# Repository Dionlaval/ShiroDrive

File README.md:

# ShiroDrive

ShiroDrive is an independent motion-control project focused on modular motor-drive hardware and experimental robotic systems.

The current hardware direction includes both stepper control and compact, networked FOC servo modules.

This is an evolving engineering project.

---

## Core Direction

ShiroDrive currently explores:

- Custom stepper motor driver design
- Dynamic microstepping techniques
- Smooth motion across wide velocity ranges
- Resonance mitigation and control refinement
- CoreXY motion architectures

The stepper platform uses ESP32, while ShiroFOC is based on the STSPIN32G4 with its embedded STM32G431 motor-control MCU.

ESP32 provides:

- Real-time capable control
- Flexible peripheral configuration
- Wireless debugging and telemetry
- Rapid prototyping flexibility

STSPIN32G4 provides:

- Integrated STM32G4 real-time motor-control MCU
- Three external-MOSFET gate drivers
- Integrated current-sense op-amps and hardware protection comparators
- CAN-based modular communication
- Compact single-axis FOC architecture

---

## Building Block

### ShiroDrive Step

A custom stepper motor control platform.

Focus areas:

- Dynamic microstepping
- High-speed stability
- Clean current control
- Modular PCB design
- Firmware-driven motion refinement

This board forms the foundation of all current machines.

### ShiroFOC

A single-axis, 48 V-class FOC servo module for robotics.

Planned features include:

- STSPIN32G4 controller and external three-phase MOSFET bridge
- Three-shunt phase-current sensing
- CAN communication to a coordinating motherboard
- Integrated magnetic encoder and 6-axis IMU
- External Hall and encoder inputs
- SWD programming and debug

See [ShiroFOC design constraints](ShiroFOC/docs/DESIGN_CONSTRAINTS.md) for the preliminary Rev A targets.

---

## Experimental Machine

### Manga Draw

A CoreXY-based pen plotting platform.

Purpose:

- Investigate high-speed planar motion
- Develop scalable XY architecture
- Render anime-style posters and manga panels with precision
- Serve as a validation platform for ShiroDrive Step

The architecture is designed to scale beyond desktop format.

---

## Development Status

### Currently Working On

- ShiroDrive Step PCB iteration
- Motion firmware development (ESP32)
- CoreXY Manga Draw platform integration

### Next Steps

- Refinement of dynamic microstepping
- Mechanical rigidity improvements
- Higher current driver revisions
- Closed-loop motion experimentation

---

ShiroDrive documents the process of building motion systems from first principles — hardware, firmware, and mechanical integration.

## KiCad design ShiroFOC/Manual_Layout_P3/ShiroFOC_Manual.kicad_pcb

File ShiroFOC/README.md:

# ShiroFOC workspace

## Start here

- **[Manual rebuild](Manual_Rebuild/ShiroFOC_Manual.kicad_pro)** — complete reference schematic with your manual MOSFET bridge retained, ready for page-by-page review; [library instructions](Manual_Rebuild/README.md).
- [P1 reference project](ShiroFOC_KiCad_P1/ShiroFOC_KiCad.kicad_pro) — existing schematic and revised component placement.
- [Saved routing review](routing_review_2026-09-21/README.md) — independent snapshots of the incomplete routing, paused for review.
- [Learning lab](../learning/README.md) — interactive models, exercises and explanations.

The original design files remain in their project folders. Routing is incomplete; the saved boards are not fabrication releases. The notes below document different design stages.

## Design notes

### Schematic and firmware

- **[Current firmware requirements](requirements/FIRMWARE_REQUIREMENTS.md)** — manual rebuild: safe startup, persistent BOOT0, calibration storage, sensors, current protection and brake control.

- [Design constraints](docs/DESIGN_CONSTRAINTS.md)
- [Rev A schematic plan](docs/SCHEMATIC_REV_A_PLAN.md)
- [Rev A design review](docs/DESIGN_REVIEW_REV_A.md)
- [Schematic readability plan](docs/SCHEMATIC_READABILITY_PLAN.md)
- [Schematic redraw review](docs/SCHEMATIC_REDRAW_REVIEW.md)
- [MCU pinout and interfaces](docs/MCU_PINOUT_AND_INTERFACE_PLAN.md)
- [Historical A0 firmware bring-up contract](docs/FIRMWARE_BRINGUP_CONTRACT.md)

### PCB

- [Layout guidelines and DRC settings](docs/PCB_LAYOUT_GUIDELINES.md)
- [Layout handoff](docs/PCB_LAYOUT_HANDOFF.md)
- [Original placement notes](docs/PCB_PLACEMENT_P0.md)
- [Revised placement notes](docs/PCB_PLACEMENT_P1.md)
- [P1 revision list](docs/PCB_REVISION_LIST_P1.md)
- [Capacitor options study](docs/PCB_CAPACITOR_OPTIONS_2026-09-17.md)

## Folder guide

| Folder | Contents |
|---|---|
| `Manual_Rebuild/` | Your schematic review copy, imported CAD and download checklist |
| `requirements/` | Current implementation requirements for the manual rebuild |
| `docs/` | Design plans, decisions and review notes |
| `ShiroFOC_KiCad/` | Original reference project and its outputs |
| `ShiroFOC_KiCad_P1/` | Revised placement project and routing experiments |
| `routing_review_2026-09-21/` | Saved routing checkpoints for inspection |
| `tools/` | Existing generation, checking and routing scripts |
| `backups/` | Preserved files, including the notes before this cleanup |

The documentation cleanup moved notes and repaired links; it did not change the existing circuitry or routing.

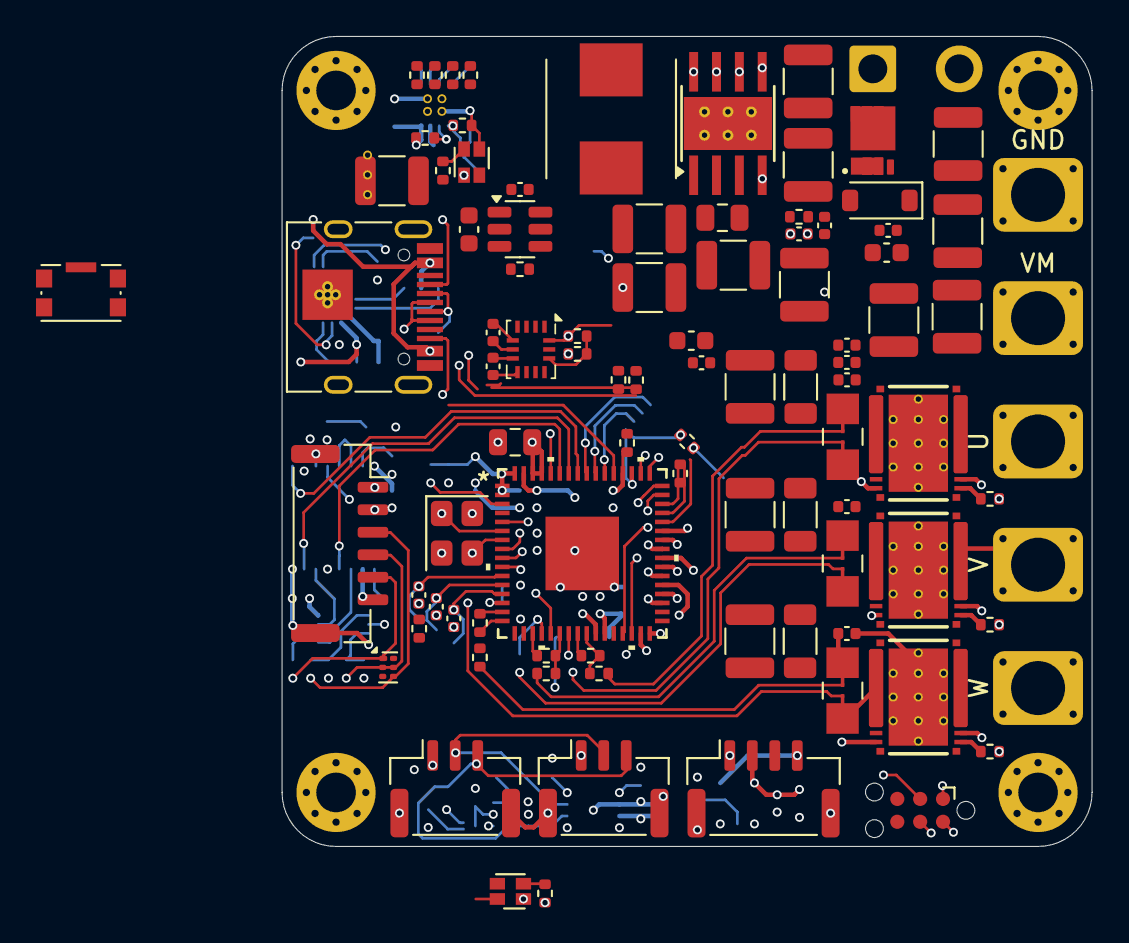
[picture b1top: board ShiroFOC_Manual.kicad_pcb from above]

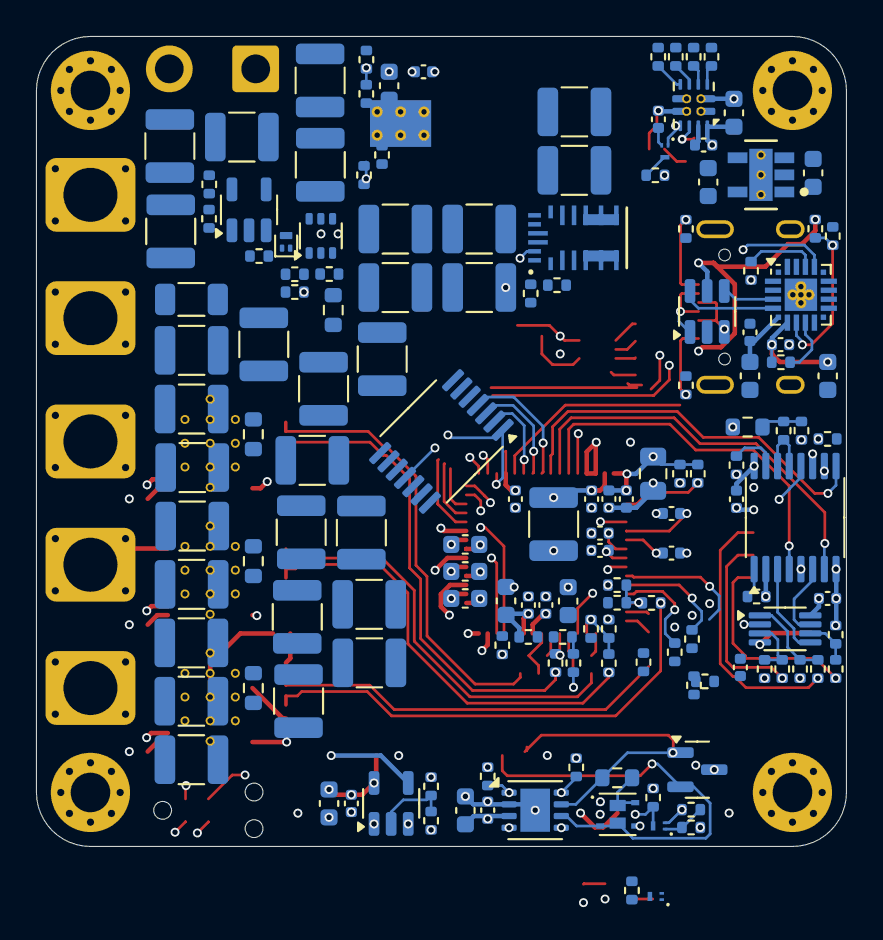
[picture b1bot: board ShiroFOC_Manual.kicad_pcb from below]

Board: 6 copper layers, 45.0 x 45.0 mm, 244 parts (149 on the bottom side), 142 nets.

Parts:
C1, C5, C9, C108, C314, C711, C712, C713: 10nF; C_0402_1005Metric
C2, C6, C10: 1uF; C_1206_3216Metric
C3, C7, C11, C101, C102, C110, C111, C112, C113, C114, C116, C117, C122, C123, C124, C127, C128, C129, C131, C133, C134, C135, C136, C137, C138, C144, C145, C146, C149, C150, C151, C152, C153, C154: 10uF; C_1210_3225Metric
C4, C8, C12: 220nF; C_0603_1608Metric
C104: 4.7uF 100V X7R; C_1210_3225Metric
C105: 100nF 100V X7R; C_0402_1005Metric
C106: 10nF 100V C0G; C_0402_1005Metric
C201: 2.2uF 100V X7R; C_1210_3225Metric
C202: 220nF 100V X7R; C_0805_2012Metric
C203, C209, C211, C301, C303, C305, C307, C310, C505, C601, C603, C605, C701, C702, C801, C902, C904: 100nF; C_0402_1005Metric
C204, C304, C306, C602, C802: 1uF; C_0603_1608Metric
C205, C206, C214, C215: 22uF 25V X7R; C_1210_3225Metric
C208: 1uF 10V; C_0603_1608Metric
C210: 22uF 10V X7R; C_1210_3225Metric
C212, C213: 2.2uF 10V X7R; C_0603_1608Metric
C218, C219: 22uF 16V X7R; C_1210_3225Metric
C302: 10uF 10V; C_0805_2012Metric
C308, C309: 10pF C0G; C_0402_1005Metric
C311: 220nF 100V; C_0805_2012Metric
C312: 10uF 25V X7R; C_1210_3225Metric
C313: 100nF 25V; C_0402_1005Metric
C501: 1uF 25V; C_0603_1608Metric
C502, C503, C604: 100nF 50V; C_0402_1005Metric
C504: 1nF C0G; C_0402_1005Metric
C506, C606: 4.7uF; C_0603_1608Metric
C607: 100nF 16V X7R; C_0402_1005Metric
C901, C903: 4.7uF 10V; C_0603_1608Metric
D201, D301: LTST-C19HE1WT; LED_LiteOn_LTST-C19HE1WT
D501: BZT52C12 12V; D_SOD-123
D502: BAT54CM; SOT-883
D601: TPD3E001DRYR; TPD3E001_DRY6
D801: PESD2CANFD24V-T; SOT-23
H1, H2, H3, H4: M2 PTH; MountingHole_2.2mm_M2_Pad_Via
J1: Motor phases - solder wires; WireSolder_Phase_1x03_P6.85mm_D3.00mm_Pad5.00x4.10mm_4xD0.4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
J101: DC input - solder wires; WireSolder_DC_1x02_P6.85mm_D3.00mm_Pad5.00x4.10mm_4xD0.40mm
J201: USB-C service; USB_C_Receptacle_HRO_TYPE-C-31-M-12
J501: BRAKE RESISTOR; SolderWire-0.75sqmm_1x02_P4.8mm_D1.25mm_OD2.3mm
J502: 5V PWM FAN; JST_GH_SM04B-GHS-TB_1x04-1MP_P1.25mm_Horizontal
J601: EXT ENCODER / HALL; JST_GH_SM06B-GHS-TB_1x06-1MP_P1.25mm_Horizontal
J801: CAN 1; JST_GH_SM03B-GHS-TB_1x03-1MP_P1.25mm_Horizontal
J802: CAN 2; JST_GH_SM03B-GHS-TB_1x03-1MP_P1.25mm_Horizontal
J1001: TC2030-NL SWD; Tag-Connect_TC2030-IDC-NL_2x03_P1.27mm_Vertical
L201: 47uH / 1.9A; WE_LHMI_7050_74437349470
Q201, Q301, Q801: CSD17483F4; CSD17483F4_YJC0003A
Q501: ISZ080N10NM6 100V; ISZ080N10NM6_TSDSON8_FL
Q802: CSD87502Q2; CSD87502Q2_DLV0006A
R1, R3, R5: 0.5m 1%; R_Shunt_HCS1206_0m5_2W_Kelvin
R2, R4, R6: 4R7; R_0402_1005Metric
R101: 470k 0.25W; R_1206_3216Metric
R103: 560k 0.1% 75V; R_0603_1608Metric
R105, R419, R429, R439: 28k 0.1%; R_0402_1005Metric
R106, R312, R711, R712, R713, R901: 1k; R_0402_1005Metric
R201: 100k 1%; R_0402_1005Metric
R202: 11.1k 1%; R_0402_1005Metric
R203, R204: 5.1k; R_0402_1005Metric
R206: 10.0k 1%; R_0402_1005Metric
R207, R209, R211, R213: 5.10k 1%; R_0402_1005Metric
R208: 15.0k 1%; R_0402_1005Metric
R210, R212: 22.0k 1%; R_0402_1005Metric
R214: 80.6k 1%; R_0402_1005Metric
R215, R220, R305, R306, R307, R309, R311, R315, R501, R504, R505, R604, R801, R805, R806: 10k; R_0402_1005Metric
R216: 34.0k 0.1%; R_0402_1005Metric
R217: 6.49k 0.1%; R_0402_1005Metric
R218, R219, R310, R512, R615, R616, R617, R804: 100k; R_0402_1005Metric
R221: 33k; R_0402_1005Metric
R301, R302: 0R; R_0402_1005Metric
R303: 2k2; R_0402_1005Metric
R304: 15k; R_0402_1005Metric
R308, R715: 2.2k; R_0402_1005Metric
R410, R420, R430, R441, R442, R443: 56k 0.1%; R_0402_1005Metric
R417, R418, R427, R428, R437, R438: 1k 0.1%; R_0402_1005Metric
R502: 33R; R_0402_1005Metric
R503: 4.7R; R_0402_1005Metric
R506: 470k 1% 75V; R_0603_1608Metric
R509: 13.3k 1%; R_0402_1005Metric
R510: 1M 1%; R_0402_1005Metric
R511, R605, R606, R607, R902, R903: 100R; R_0402_1005Metric
R618: 49.9k 1%; R_0402_1005Metric
R701, R702, R703: 4.7k 1%; R_0402_1005Metric
R802: 120R 1%; R_0603_1608Metric
R803: 4.7k; R_0402_1005Metric
R904: 22.1k 1%; R_0402_1005Metric
R905: 47.5k 1%; R_0402_1005Metric
SW301: RESET; SW_Push_1P1T-SH_NO_CK_KMR2xxG
TH701, TH702, TH703: 10k NTC B3380; R_0603_1608Metric
U1, U2, U3: CSD88599Q5DC; DMM0022A
U4: STSPIN32G4; QFN_IN32G4_STM
U201: LMR36510FADDAR; LMR36510_DDA
U202: USBLC6-2SC6; USBLC6_SOT23_6
U203: TPS2121RUXR; TPS2121_RUX
U204: TLV75533PDYDR; TLV75533_DYD_GND
U205: MPM3620AGQV-Z; IC18_MPM3620AGQV-Z_MNP
U501: UCC27517ADBVR; UCC27517A_DBV5
U502: TLV3012BIDCKR; SOT-363_SC-70-6
U503: 74AHCT1G125W5-7; SOT-23-5
U601: AS5047P-ATSM; AS5047P_TSSOP14
U602: TMUX1574PW; TMUX1574_PW16
U603: 74LVC3G17; VSSOP-8_2.3x2mm_P0.5mm
U604: TPS2553DBVR; SOT-23-6
U701: BMI323; BMI323_LGA14
U801: TCAN3413DRBR; TCAN3413_DRB8
U901: CP2102N-A02-GQFN20; SiliconLabs_QFN-20-1EP_3x3mm_P0.5mm_EP1.8x1.8mm_ThermalVias
Y301: 24MHz 7pF; Crystal_SMD_3225-4Pin_3.2x2.5mm

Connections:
3V3: C213.1, C301.1, C302.1, C307.1, C503.1, C601.1, C602.1, C603.1, C605.1, C701.1, C702.1, C801.1, C802.1, C901.1, C902.1, C903.1, C904.1, J1001.1 (VCC), R301.1, R303.1, R305.1, R308.1, R309.1, R310.1, R604.1, R701.1, R702.1, R703.1, R715.1, R801.1, R805.1, R901.1, U4.1 (REG3V3/VDD), U4.2 (VBAT), U4.64 (REGIN), U204.5 (OUT), U502.6 (VDD), U601.11 (VDD), U601.12 (VDD3V3), U602.16 (VDD), U603.8 (VCC), U701.5 (VDDIO), U701.8 (VDD), U701.12 (CSB), U801.3 (VCC), U801.5 (VIO), U901.6 (VDD), U901.7 (VREGIN)
5V_BAT: C218.1, C219.1, R206.1, R210.1, R216.1, U203.7 (IN1), U205.7 (OUT), U205.8 (OUT), U205.9 (OUT)
5V_SYS: C210.1, C211.1, C212.1, C606.1, D201.4 (A), D301.4 (A), R215.1, U203.1 (OUT), U203.8 (OUT), U204.1 (IN), U204.3 (EN), U604.1 (IN), U604.3 (EN)
5V_USB: C208.1, J201.A4 (VBUS), J201.A9 (VBUS), J201.B4 (VBUS), J201.B9 (VBUS), R208.1, R212.1, R904.1, U202.5 (VBUS), U203.2 (IN2)
/5 V / 3.3 V power/10V_FB: R201.2, R202.1, U201.5 (FB)
/5 V / 3.3 V power/10V_GOOD: R218.2, R219.1, U201.4 (PG), U205.17 (EN)
/5 V / 3.3 V power/U205_AGND: R217.2, U205.3 (AGND)
/5 V / 3.3 V power/U205_SW: U205.4 (SW), U205.5 (SW), U205.6 (SW)
/Brake chopper/BRAKE_OV_CMD: D502.2 (A2), R510.1, U502.1 (OUT)
/Brake chopper/BRAKE_PWM_DRV: D502.3 (CC), R505.1, U501.3 (IN+)
/Brake chopper/FAN_PWM_5V: J502.4 (PWM), U503.4 (Y)
/CAN interface/CANH_BUS: D801.1 (CANH_IN), J801.2 (CANH), J802.2 (CANH), R802.1, U801.7 (CANH)
/CAN interface/CANL_BUS: D801.2 (CANL_IN), J801.3 (CANL), J802.3 (CANL), Q802.3 (D2), U801.6 (CANL)
/Current / temperature/NTC_A_RAW: R702.2, R712.1, TH702.1
/Current / temperature/NTC_B_RAW: R701.2, R711.1, TH701.1
/Current / temperature/NTC_C_RAW: R703.2, R713.1, TH703.1
/Current / temperature/OPN_U1: R438.2, R439.2, U4.25 (-)
/Current / temperature/OPN_V1: R428.2, R429.2, U4.22 (-)
/Current / temperature/OPN_W1: R418.2, R419.2, U4.16 (-)
/Current / temperature/OPP_U1: R430.2, R437.2, R443.1, U4.23 (+)
/Current / temperature/OPP_V1: R420.2, R427.2, R442.1, U4.20 (+)
/Current / temperature/OPP_W1: R410.2, R417.2, R441.1, U4.14 (+)
/External feedback/FB_ESD_RAIL: C604.1, D601.6 (VCC)
/MCU / clock / SWD/NRST: C310.1, J1001.3 (~RESET), R303.2, SW301.1, U4.8 (PG10/NRST)
/MCU / clock / SWD/SWCLK: J1001.4 (SWCLK), U4.50 (PA14/SWCLK)
/MCU / clock / SWD/SWDIO: J1001.2 (SWDIO), U4.49 (PA13/SWDIO)
/Three-phase bridge/LS_SOURCE_U: R3.1 (POWER+), U1.12 (PGND), U1.13 (PGND), U1.14 (PGND), U1.15 (PGND), U1.16 (PGND), U1.17 (PGND), U1.18 (PGND), U1.19 (PGND), U1.20 (PGND)
/Three-phase bridge/LS_SOURCE_V: R1.1 (POWER+), U2.12 (PGND), U2.13 (PGND), U2.14 (PGND), U2.15 (PGND), U2.16 (PGND), U2.17 (PGND), U2.18 (PGND), U2.19 (PGND), U2.20 (PGND)
/Three-phase bridge/LS_SOURCE_W: R5.1 (POWER+), U3.12 (PGND), U3.13 (PGND), U3.14 (PGND), U3.15 (PGND), U3.16 (PGND), U3.17 (PGND), U3.18 (PGND), U3.19 (PGND), U3.20 (PGND)
/USB service/CP2102_RST_N: R901.2, U901.9 (RST)
/USB service/CP2102_VBUS_SENSE: R904.2, R905.1, U901.8 (VBUS)
/USB service/UART_BRIDGE_RX: R903.2, U901.17 (RXD)
/USB service/UART_BRIDGE_TX: R902.1, U901.18 (TXD)
/USB service/USB_CC1: J201.A5 (CC1), R203.1
/USB service/USB_CC2: J201.B5 (CC2), R204.1
/USB service/USB_DM: U202.6 (IO1), U901.5 (D-)
/USB service/USB_DM_CONN: J201.A7 (D-), J201.B7 (D-), U202.1 (IO1)
/USB service/USB_DP: U202.4 (IO2), U901.4 (D+)
/USB service/USB_DP_CONN: J201.A6 (D+), J201.B6 (D+), U202.3 (IO2)
AS5047P_CS_N: R309.2, U4.51 (PA15), U601.1 (CSn)
BOOTSTRAP1: C4.2, U4.41 (BOOTSTRAP1)
BOOTSTRAP2: C8.2, U4.38 (BOOTSTRAP2)
BOOTSTRAP3: C12.2, U4.35 (BOOTSTRAP3)
BRAKE_PWM: R501.1, R502.1, U4.60 (PB9)
CAN_STB: R801.2, U4.28 (PB10), U801.8 (STB)
CAN_TERM_DISABLE: R803.1, U4.5 (PC15)
CAN_TERM_GATE: Q301.1 (G), Q801.3 (D), Q802.2 (G1), Q802.5 (G2), R806.2
EXT_FEEDBACK_SELECT: R306.1, U4.53 (PD2), U602.1 (SEL)
EXT_POWER_FAULT_N: R604.2, U4.3 (PC13), U604.4 (~FAULT)
EXT_VCC: C505.1, C506.1, C607.1, J502.2 (+5V), J601.1, U503.5 (VCC), U604.6 (OUT)
FAN_PWM: R511.1, U4.10 (PC1)
FDCAN1_RX: U4.47 (PA11), U801.4 (RXD)
FDCAN1_TX: R805.2, U4.48 (PA12), U801.1 (TXD)
FEEDBACK_A_H1: U4.57 (PB6), U602.9 (D3)
FEEDBACK_B_H2: U4.58 (PB7), U602.7 (D2)
FEEDBACK_I_H3: R307.1, U4.59 (PB8/BOOT0), U602.4 (D1)
GHS1: R2.2, U4.43 (GHS1)
GHS2: R4.2, U4.40 (GHS2)
GHS3: R6.2, U4.37 (GHS3)
GLS1: U1.22 (GL), U4.29 (GLS1)
GLS2: U2.22 (GL), U4.30 (GLS2)
GLS3: U3.22 (GL), U4.31 (GLS3)
GND: C1.2, C2.2, C3.2, C5.2, C6.2, C7.2, C9.2, C10.2, C11.2, C101.2, C102.2, C104.2, C105.2, C106.2, C108.2, C110.2, C111.2, C112.2, C113.2, C114.2, C116.2, C117.2, C122.2, C123.2, C124.2, C127.2, C128.2, C129.2, C131.2, C133.2, C134.2, C135.2, C136.2, C137.2, C138.2, C144.2, C145.2, C146.2, C149.2, C150.2, C151.2, C152.2, C153.2, C154.2, C201.2, C202.2, C204.2, C205.2, C206.2, C208.2, C209.2, C210.2, C211.2, C212.2, C213.2, C214.2, C215.2, C218.2, C219.2, C301.2, C302.2, C303.2, C304.2, C305.2, C306.2, C307.2, C308.2, C309.2, C310.2, C311.2, C312.2, C313.2, C314.2, C501.2, C502.2, C503.2, C504.2, C505.2, C506.2, C601.2, C602.2, C603.2, C604.2, C605.2, C606.2, C607.2, C701.2, C702.2, C711.2, C712.2, C713.2, C801.2, C802.2, C901.2, C902.2, C903.2, C904.2, D501.2 (A), D601.3 (GND), D801.3 (GND), J101.1, J201.A1 (GND), J201.A12 (GND), J201.B1 (GND), J201.B12 (GND), J201.S1 (SHIELD), J502.1 (GND), J502.MP (MOUNT), J601.2, J601.6, J601.MP (MOUNT), J801.1 (GND), J801.MP (MOUNT), J802.1 (GND), J802.MP (MOUNT), J1001.5 (GND), Q201.2 (S), Q301.2 (S), Q501.1 (S), Q501.2 (S), Q501.3 (S), Q801.2 (S), R1.4 (POWER-), R3.4 (POWER-), R5.4 (POWER-), R101.2, R105.2, R202.2, R203.2, R204.2, R207.2, R209.2, R211.2, R213.2, R214.2, R219.2, R220.2, R306.2, R307.2, R311.2, R315.2, R441.2, R442.2, R443.2, R501.2, R504.2, R505.2, R509.2, R512.2, R615.2, R616.2, R617.2, R618.2, R804.2, R905.2, SW301.2, SW301.SH (B), TH701.2, TH702.2, TH703.2, U4.32 (PGND), U4.65 (VSS/EP), U201.1 (PGND), U201.9 (GND), U202.2 (GND), U203.12 (GND), U204.2 (GND), U205.12 (PGND), U205.13 (PGND), U205.14 (PGND), U501.2 (GND), U501.4 (IN-), U502.2 (GND), U503.1 (~OE), U503.3 (GND), U601.5 (TEST), U601.13 (GND), U602.2 (S1A), U602.5 (S2A), U602.8 (GND), U602.11 (S3A), U603.4 (GND), U604.2 (GND), U701.1 (SDO/SA0), U701.6 (GNDIO), U701.7 (GND), U801.2 (GND), U801.9 (EP), U901.3 (GND), U901.12 (GND), U901.21 (EP), Y301.2, Y301.4
HS_RETURN_U: C4.1, U1.2 (SH), U4.42 (OUT1)
HS_RETURN_V: C8.1, U2.2 (SH), U4.39 (OUT2)
HS_RETURN_W: C12.1, U3.2 (SH), U4.36 (OUT3)
I2C2_SCL: R308.2, U4.21 (PC4), U701.13 (SCK/SCL)
I2C2_SDA: R715.2, U4.44 (PA8), U701.14 (SDI/SDA)
IMU_INT1: U4.17 (PA4), U701.4 (INT1)
IMU_INT2: U4.18 (PA5), U701.9 (INT2)
INPUT_MUX_ENABLE_N: R305.2, U4.4 (PC14), U602.15 (EN_N)
NTC_PHASE_A: C712.1, R712.2, U4.11 (PC2)
NTC_PHASE_B: C711.1, R711.2, U4.12 (PC3)
NTC_PHASE_C: C713.1, R713.2, U4.13 (PA0)
unnamed: D201.3 (BK), R220.1
unnamed: D201.2 (GK), R221.1
unnamed: D301.3 (BK), R315.1
unnamed: D301.1 (RK), R304.2
unnamed: D501.1 (K), Q501.4 (G), R503.2, R504.1
unnamed: D502.1 (A1), R502.2
unnamed: D601.1 (IO1), J601.5, R607.1
unnamed: D601.2 (IO2), D601.5 (NC), J601.4, R606.1
unnamed: D601.4 (IO3), J601.3, R605.1
unnamed: J501.1, Q501.5 (D), Q501.6 (D), Q501.7 (D), Q501.8 (D)
unnamed: Q201.3 (D), R221.2
unnamed: Q301.3 (D), R304.1
unnamed: Q801.1 (G), R803.2, R804.1
unnamed: Q802.6 (D1), R802.2
unnamed: Q802.1 (S1), Q802.4 (S2)
unnamed: R103.2, R105.1, R106.1
unnamed: R310.2, R311.1, R312.1
unnamed: R605.2, R615.1, U603.1
unnamed: R606.2, R616.1, U603.3
unnamed: R607.2, R617.1, U603.6
unnamed: R2.1, U1.1 (GH)
unnamed: R4.1, U2.1 (GH)
unnamed: R6.1, U3.1 (GH)
unnamed: C308.1, U4.6 (PF0), Y301.1
unnamed: C309.1, U4.7 (PF1), Y301.3
unnamed: C314.1, R312.2, U4.52 (SCREF)
unnamed: C203.1, U201.7 (BOOT)
unnamed: C203.2, L201.1, U201.8 (SW)
unnamed: C204.1, U201.6 (VCC)
unnamed: R208.2, R209.1, U203.3 (CP2)
unnamed: R214.1, U203.10 (ILM)
unnamed: R210.2, R211.1, U203.5 (OV1)
unnamed: R212.2, R213.1, U203.4 (OV2)
unnamed: R206.2, R207.1, U203.6 (PR1)
unnamed: C209.1, U203.11 (SS)
unnamed: R216.2, R217.1, U205.1 (FB)
unnamed: R503.1, U501.5 (OUT)
unnamed: C504.1, R506.2, R509.1, R510.2, U502.3 (IN+)
unnamed: U502.4 (IN-), U502.5 (REF)
unnamed: R511.2, R512.1, U503.2 (A)
unnamed: U602.3 (S1B), U603.5
unnamed: U602.6 (S2B), U603.7
unnamed: U602.10 (S3B), U603.2
unnamed: R618.1, U604.5 (ILIM)
OPO_U1: R439.1, U4.24 (OUT)
OPO_V1: R429.1, U4.19 (OUT)
OPO_W1: R419.1, U4.15 (OUT)
PHASE_U: J1.1 (U), U1.3 (VSW), U1.4 (VSW), U1.5 (VSW), U1.6 (VSW), U1.7 (VSW), U1.8 (VSW), U1.9 (VSW), U1.10 (VSW), U1.11 (VSW)
PHASE_V: J1.2 (V), U2.3 (VSW), U2.4 (VSW), U2.5 (VSW), U2.6 (VSW), U2.7 (VSW), U2.8 (VSW), U2.9 (VSW), U2.10 (VSW), U2.11 (VSW)
PHASE_W: J1.3 (W), U3.3 (VSW), U3.4 (VSW), U3.5 (VSW), U3.6 (VSW), U3.7 (VSW), U3.8 (VSW), U3.9 (VSW), U3.10 (VSW), U3.11 (VSW)
PWR_SOURCE_STATUS: Q201.1 (G), R215.2, U203.9 (ST)
SHUNT_U_SENSE_N: R3.3 (SENSE-), R438.1
SHUNT_U_SENSE_P: R3.2 (SENSE+), R437.1
SHUNT_V_SENSE_N: R1.3 (SENSE-), R428.1
SHUNT_V_SENSE_P: R1.2 (SENSE+), R427.1
SHUNT_W_SENSE_N: R5.3 (SENSE-), R418.1
SHUNT_W_SENSE_P: R5.2 (SENSE+), R417.1
SPI3_MISO: U4.55 (PB4), U601.3 (MISO)
SPI3_MOSI_MCU: U4.56 (PB5), U601.4 (MOSI)
SPI3_SCK_MCU: U4.54 (PB3), U601.2 (CLK)
USB_UART_RX: R902.2, U4.46 (PA10)
USB_UART_TX: R903.1, U4.45 (PA9)
VBUS_MUX_IN: R106.2, U602.13 (S4A), U602.14 (S4B)
VBUS_SENSE: C108.1, U4.9 (PC0), U602.12 (D4)
VCC: C205.1, C206.1, C214.1, C215.1, C312.1, C313.1, C501.1, C502.1, L201.2, R201.1, R218.1, R806.1, U4.63 (VCC), U205.16 (IN), U501.1 (VDD)
VDDA: C303.1, C304.1, R301.2, R302.1, U4.27 (VDDA)
VM: C1.1, C2.1, C3.1, C5.1, C6.1, C7.1, C9.1, C10.1, C11.1, C101.1, C102.1, C104.1, C105.1, C106.1, C110.1, C111.1, C112.1, C113.1, C114.1, C116.1, C117.1, C122.1, C123.1, C124.1, C127.1, C128.1, C129.1, C131.1, C133.1, C134.1, C135.1, C136.1, C137.1, C138.1, C144.1, C145.1, C146.1, C149.1, C150.1, C151.1, C152.1, C153.1, C154.1, C201.1, C202.1, C311.1, J101.2, J501.2, R101.1, R103.1, R506.1, U1.27 (VIN), U2.27 (VIN), U3.27 (VIN), U4.61 (VM), U4.62 (SW), U201.2 (VIN), U201.3 (EN)
VREF+: C305.1, C306.1, R302.2, R410.1, R420.1, R430.1, U4.26 (VREF+)

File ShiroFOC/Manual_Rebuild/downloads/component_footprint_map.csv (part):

References,Page / function,MPN,Value,Footprint,Footprint resolves,3D model paths,CAD status,Assembly,Datasheet
H1,/,,M3 NPTH,MountingHole:MountingHole_3.2mm_M3,True,,Assigned; footprint file resolves. See review for qualification limits.,,
H2,/,,M3 NPTH,MountingHole:MountingHole_3.2mm_M3,True,,Assigned; footprint file resolves. See review for qualification limits.,,
H3,/,,M3 NPTH,MountingHole:MountingHole_3.2mm_M3,True,,Assigned; footprint file resolves. See review for qualification limits.,,
H4,/,,M3 NPTH,MountingHole:MountingHole_3.2mm_M3,True,,Assigned; footprint file resolves. See review for qualification limits.,,
C101,/DC link / input/,EEVFK1J681M,680uF 63V,Manual:Panasonic_EEVFK_K16_18x16.5,True,${KICAD9_3DMODEL_DIR}/Capacitor_SMD.3dshapes/CP_Elec_18x17.5.step,Footprint present; generic model is approximate envelope.,FIT,
C102,/DC link / input/,EEVFK1J681M,680uF 63V,Manual:Panasonic_EEVFK_K16_18x16.5,True,${KICAD9_3DMODEL_DIR}/Capacitor_SMD.3dshapes/CP_Elec_18x17.5.step,Footprint present; generic model is approximate envelope.,FIT,
C103,/DC link / input/,EEVFK1J681M,680uF 63V,Manual:Panasonic_EEVFK_K16_18x16.5,True,${KICAD9_3DMODEL_DIR}/Capacitor_SMD.3dshapes/CP_Elec_18x17.5.step,Footprint present; generic model is approximate envelope.,FIT,
C104,/DC link / input/,,4.7uF 100V X7R,Capacitor_SMD:C_1210_3225Metric,True,${KICAD9_3DMODEL_DIR}/Capacitor_SMD.3dshapes/C_1210_3225Metric.step,Assigned; footprint file resolves. See review for qualification limits.,FIT,
C105,/DC link / input/,,100nF 100V X7R,Capacitor_SMD:C_0805_2012Metric,True,${KICAD9_3DMODEL_DIR}/Capacitor_SMD.3dshapes/C_0805_2012Metric.step,Assigned; footprint file resolves. See review for qualification limits.,FIT,
C106,/DC link / input/,,10nF 100V C0G,Capacitor_SMD:C_0603_1608Metric,True,${KICAD9_3DMODEL_DIR}/Capacitor_SMD.3dshapes/C_0603_1608Metric.step,Assigned; footprint file resolves. See review for qualification limits.,FIT,
C107,/DC link / input/,,RC DAMP C - TUNE,Capacitor_SMD:C_2220_5750Metric,True,${KICAD9_3DMODEL_DIR}/Capacitor_SMD.3dshapes/C_2220_5750Metric.step,Assigned; footprint file resolves. See review for qualification limits.,DNP,
C108,/DC link / input/,,10nF,Capacitor_SMD:C_0603_1608Metric,True,${KICAD9_3DMODEL_DIR}/Capacitor_SMD.3dshapes/C_0603_1608Metric.step,Assigned; footprint file resolves. See review for qualification limits.,FIT,
D101,/DC link / input/,,VM TVS - SELECT AFTER TEST,Diode_SMD:D_SMC,True,${KICAD9_3DMODEL_DIR}/Diode_SMD.3dshapes/D_SMC.step,Assigned; footprint file resolves. See review for qualification limits.,DNP,
J101,/DC link / input/,XT60PW-M,AMASS XT60PW-M,Connector_AMASS:AMASS_XT60PW-M_1x02_P7.20mm_Horizontal,True,${KICAD9_3DMODEL_DIR}/Connector_AMASS.3dshapes/AMASS_XT60PW-M_1x02_P7.20mm_Horizontal.step,Footprint present; model missing (wire model optional for J501).,FIT,
R101,/DC link / input/,,470k 0.25W,Resistor_SMD:R_1206_3216Metric,True,${KICAD9_3DMODEL_DIR}/Resistor_SMD.3dshapes/R_1206_3216Metric.step,Assigned; footprint file resolves. See review for qualification limits.,FIT,
R102,/DC link / input/,,RC DAMP R - TUNE,Resistor_SMD:R_2512_6332Metric,True,${KICAD9_3DMODEL_DIR}/Resistor_SMD.3dshapes/R_2512_6332Metric.step,Assigned; footprint file resolves. See review for qualification limits.,DNP,
R103,/DC link / input/,,270k 0.1% 100V,Resistor_SMD:R_1206_3216Metric,True,${KICAD9_3DMODEL_DIR}/Resistor_SMD.3dshapes/R_1206_3216Metric.step,Assigned; footprint file resolves. See review for qualification limits.,FIT,
R104,/DC link / input/,,270k 0.1% 100V,Resistor_SMD:R_1206_3216Metric,True,${KICAD9_3DMODEL_DIR}/Resistor_SMD.3dshapes/R_1206_3216Metric.step,Assigned; footprint file resolves. See review for qualification limits.,FIT,
R105,/DC link / input/,,27k 0.1%,Resistor_SMD:R_0603_1608Metric,True,${KICAD9_3DMODEL_DIR}/Resistor_SMD.3dshapes/R_0603_1608Metric.step,Assigned; footprint file resolves. See review for qualification limits.,FIT,
R106,/DC link / input/,,1k,Resistor_SMD:R_0603_1608Metric,True,${KICAD9_3DMODEL_DIR}/Resistor_SMD.3dshapes/R_0603_1608Metric.step,Assigned; footprint file resolves. See review for qualification limits.,FIT,
TP101,/DC link / input/,PCB feature,VM,TestPoint:TestPoint_Pad_D1.5mm,True,,Assigned; footprint file resolves. See review for qualification limits.,FIT,
TP102,/DC link / input/,PCB feature,GND,TestPoint:TestPoint_Pad_D1.5mm,True,,Assigned; footprint file resolves. See review for qualification limits.,FIT,
TP103,/DC link / input/,PCB feature,VBUS_SENSE,TestPoint:TestPoint_Pad_D1.5mm,True,,Assigned; footprint file resolves. See review for qualification limits.,FIT,
C201,/5 V / 3.3 V power/,,2.2uF 100V X7R,Capacitor_SMD:C_1210_3225Metric,True,${KICAD9_3DMODEL_DIR}/Capacitor_SMD.3dshapes/C_1210_3225Metric.step,Assigned; footprint file resolves. See review for qualification limits.,FIT,
C202,/5 V / 3.3 V power/,,220nF 100V X7R,Capacitor_SMD:C_0805_2012Metric,True,${KICAD9_3DMODEL_DIR}/Capacitor_SMD.3dshapes/C_0805_2012Metric.step,Assigned; footprint file resolves. See review for qualification limits.,FIT,
C203,/5 V / 3.3 V power/,,100nF,Capacitor_SMD:C_0603_1608Metric,True,${KICAD9_3DMODEL_DIR}/Capacitor_SMD.3dshapes/C_0603_1608Metric.step,Assigned; footprint file resolves. See review for qualification limits.,FIT,
C204,/5 V / 3.3 V power/,,1uF,Capacitor_SMD:C_0603_1608Metric,True,${KICAD9_3DMODEL_DIR}/Capacitor_SMD.3dshapes/C_0603_1608Metric.step,Assigned; footprint file resolves. See review for qualification limits.,FIT,
C205,/5 V / 3.3 V power/,C3225X7R1E226M250AB,22uF 25V X7R,Capacitor_SMD:C_1210_3225Metric,True,${KICAD9_3DMODEL_DIR}/Capacitor_SMD.3dshapes/C_1210_3225Metric.step,Exact TDK part/bias curves selected; standard 1210 footprint; generic STEP height may differ (allow2.7mm),FIT,https://product.tdk.com/en/search/capacitor/ceramic/mlcc/inf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
C206,/5 V / 3.3 V power/,C3225X7R1E226M250AB,22uF 25V X7R,Capacitor_SMD:C_1210_3225Metric,True,${KICAD9_3DMODEL_DIR}/Capacitor_SMD.3dshapes/C_1210_3225Metric.step,Exact TDK part/bias curves selected; standard 1210 footprint; generic STEP height may differ (allow2.7mm),FIT,https://product.tdk.com/en/search/capacitor/ceramic/mlcc/inf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
C209,/5 V / 3.3 V power/,,100nF,Capacitor_SMD:C_0603_1608Metric,True,${KICAD9_3DMODEL_DIR}/Capacitor_SMD.3dshapes/C_0603_1608Metric.step,Assigned; footprint file resolves. See review for qualification limits.,FIT,
C210,/5 V / 3.3 V power/,,22uF 10V X7R,Capacitor_SMD:C_1210_3225Metric,True,${KICAD9_3DMODEL_DIR}/Capacitor_SMD.3dshapes/C_1210_3225Metric.step,Assigned; footprint file resolves. See review for qualification limits.,FIT,
C211,/5 V / 3.3 V power/,,100nF,Capacitor_SMD:C_0603_1608Metric,True,${KICAD9_3DMODEL_DIR}/Capacitor_SMD.3dshapes/C_0603_1608Metric.step,Assigned; footprint file resolves. See review for qualification limits.,FIT,
C212,/5 V / 3.3 V power/,,2.2uF 10V X7R,Capacitor_SMD:C_0603_1608Metric,True,${KICAD9_3DMODEL_DIR}/Capacitor_SMD.3dshapes/C_0603_1608Metric.step,Assigned; footprint file resolves. See review for qualification limits.,FIT,
C213,/5 V / 3.3 V power/,,2.2uF 10V X7R,Capacitor_SMD:C_0603_1608Metric,True,${KICAD9_3DMODEL_DIR}/Capacitor_SMD.3dshapes/C_0603_1608Metric.step,Assigned; footprint file resolves. See review for qualification limits.,FIT,
C214,/5 V / 3.3 V power/,C3225X7R1E226M250AB,22uF 25V X7R,Capacitor_SMD:C_1210_3225Metric,True,${KICAD9_3DMODEL_DIR}/Capacitor_SMD.3dshapes/C_1210_3225Metric.step,Exact TDK part/bias curves selected; standard 1210 footprint; generic STEP height may differ (allow2.7mm),FIT,https://product.tdk.com/en/search/capacitor/ceramic/mlcc/inf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
C215,/5 V / 3.3 V power/,C3225X7R1E226M250AB,22uF 25V X7R,Capacitor_SMD:C_1210_3225Metric,True,${KICAD9_3DMODEL_DIR}/Capacitor_SMD.3dshapes/C_1210_3225Metric.step,Exact TDK part/bias curves selected; standard 1210 footprint; generic STEP height may differ (allow2.7mm),FIT,https://product.tdk.com/en/search/capacitor/ceramic/mlcc/inf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
